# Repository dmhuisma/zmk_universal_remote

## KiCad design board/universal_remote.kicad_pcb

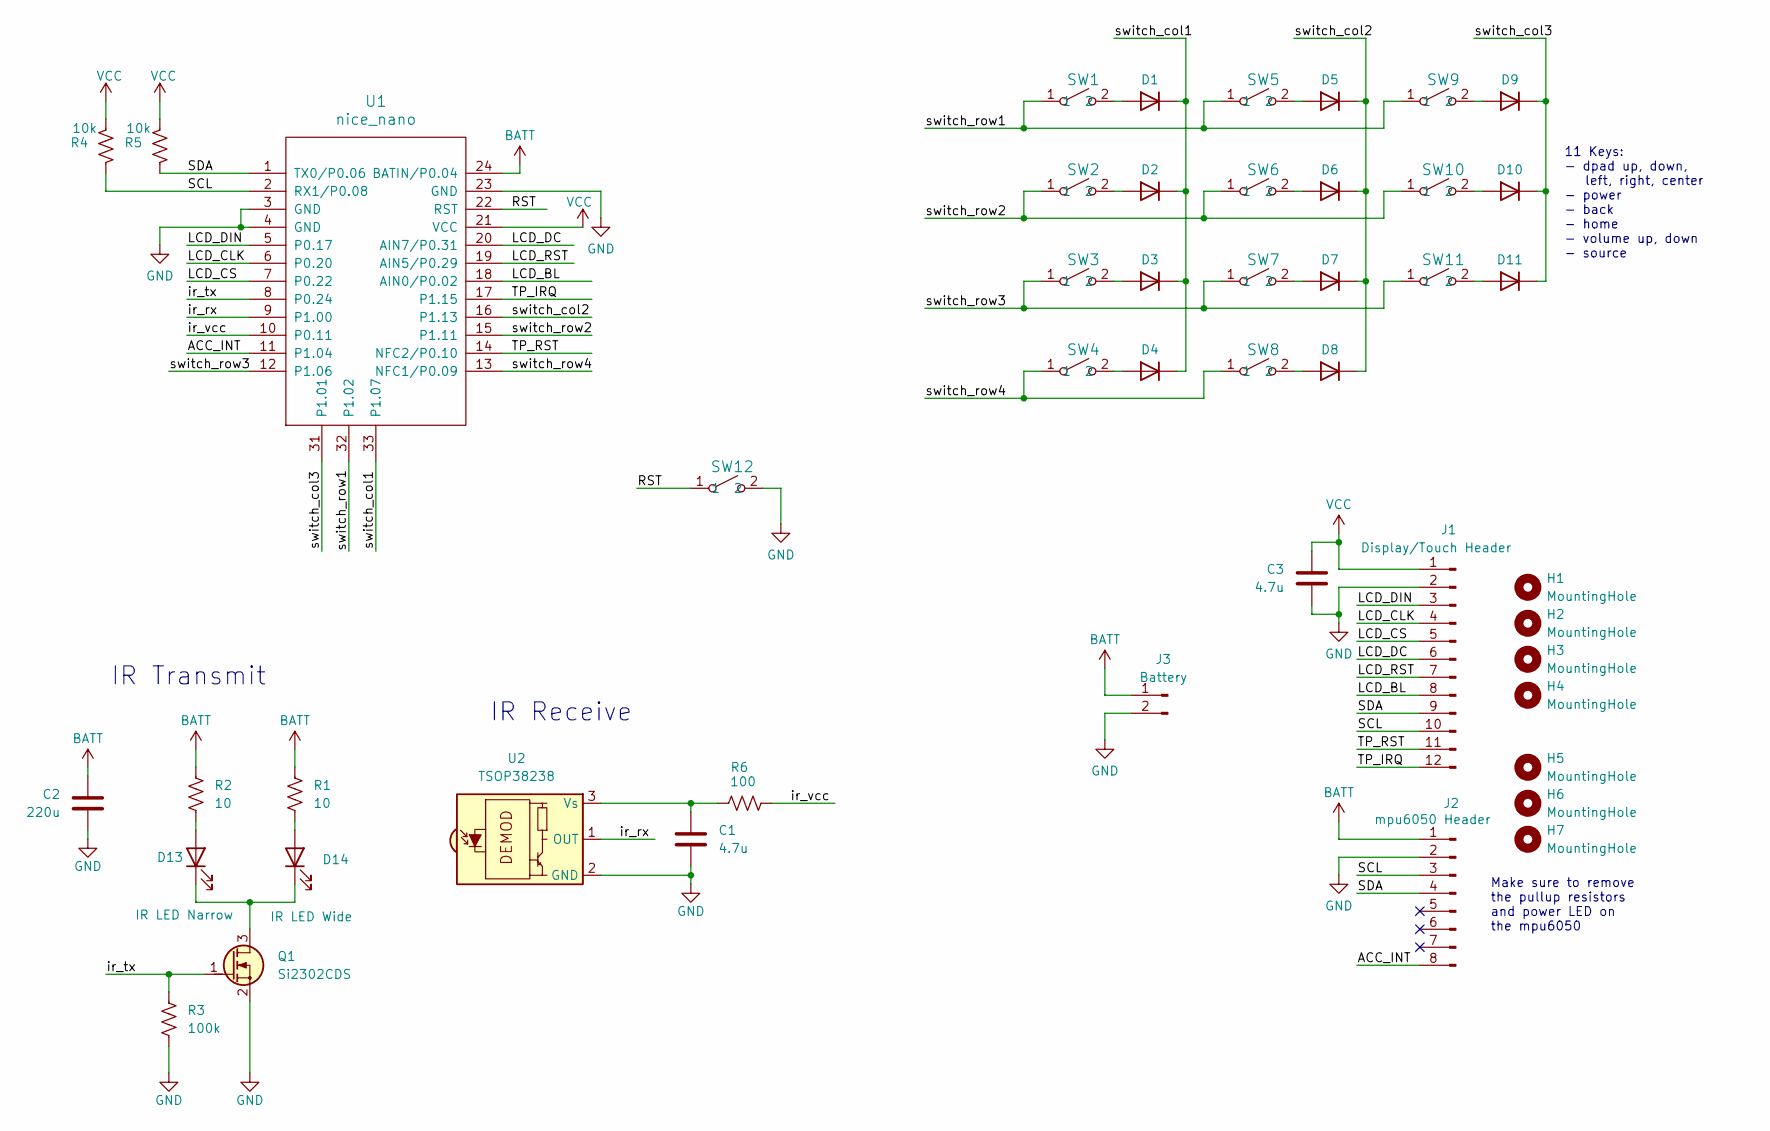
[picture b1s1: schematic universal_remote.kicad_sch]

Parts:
C1, C3: 4.7u; C_0603_1608Metric_Pad1.08x0.95mm_HandSolder
C2: 220u; C_1210_3225Metric_Pad1.33x2.70mm_HandSolder
D1, D2, D3, D4, D5, D6, D7, D8, D9, D10, D11: D; D_DO-35_SOD27_P10.16mm_Horizontal
D13: IR LED Narrow; LED_D5.0mm
D14: IR LED Wide; LED_D5.0mm
H1, H2, H3, H4: MountingHole; MountingHole_2.2mm_M2
H5, H6, H7: MountingHole; MountingHole_3.2mm_M3
J1: Display/Touch Header; PinHeader_1x12_P2.54mm_Vertical
J2: mpu6050 Header; PinHeader_1x08_P2.54mm_Vertical
J3: Battery; PinHeader_1x02_P2.54mm_Vertical
Q1: Si2302CDS; SOT-23
R1, R2: 10; R_1206_3216Metric_Pad1.30x1.75mm_HandSolder
R3: 100k; R_0603_1608Metric_Pad0.98x0.95mm_HandSolder
R4, R5: 10k; R_0603_1608Metric_Pad0.98x0.95mm_HandSolder
R6: 100; R_0603_1608Metric_Pad0.98x0.95mm_HandSolder
SW1, SW2, SW3, SW4, SW5, SW6, SW7, SW8, SW9, SW10, SW11, SW12: SKPMAME010; SKPMAME010_ALPS
U1: nice_nano
U2: TSOP38238; Vishay_MINICAST-3Pin

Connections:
/ACC_INT: J2.8, U1.11 (P1.04)
/LCD_BL: J1.8, U1.18 (AIN0/P0.02)
/LCD_CLK: J1.4, U1.6 (P0.20)
/LCD_CS: J1.5, U1.7 (P0.22)
/LCD_DC: J1.6, U1.20 (AIN7/P0.31)
/LCD_DIN: J1.3, U1.5 (P0.17)
/LCD_RST: J1.7, U1.19 (AIN5/P0.29)
/RST: SW12.1, U1.22 (RST)
/SCL: J1.10, J2.3, R4.2, U1.2 (RX1/P0.08)
/SDA: J1.9, J2.4, R5.2, U1.1 (TX0/P0.06)
/TP_IRQ: J1.12, U1.17 (P1.15)
/TP_RST: J1.11, U1.14 (NFC2/P0.10)
/ir_rx: U1.9 (P1.00), U2.1 (OUT)
/ir_tx: Q1.1 (G), R3.2, U1.8 (P0.24)
/ir_vcc: R6.2, U1.10 (P0.11)
/switch_col1: D1.1 (K), D2.1 (K), D3.1 (K), D4.1 (K), U1.33 (P1.07)
/switch_col2: D5.1 (K), D6.1 (K), D7.1 (K), D8.1 (K), U1.16 (P1.13)
/switch_col3: D9.1 (K), D10.1 (K), D11.1 (K), U1.31 (P1.01)
/switch_row1: SW1.1, SW5.1, SW9.1, U1.32 (P1.02)
/switch_row2: SW2.1, SW6.1, SW10.1, U1.15 (P1.11)
/switch_row3: SW3.1, SW7.1, SW11.1, U1.12 (P1.06)
/switch_row4: SW4.1, SW8.1, U1.13 (NFC1/P0.09)
BATT: C2.2, J2.1, J3.1, R1.1, R2.1, U1.24 (BATIN/P0.04)
GND: C1.2, C2.1, C3.1, J1.2, J2.2, J3.2, Q1.2 (S), R3.1, SW12.2, U1.3 (GND), U1.4 (GND), U1.23 (GND), U2.2 (GND)
unnamed: D1.2 (A), SW1.2
unnamed: D2.2 (A), SW2.2
unnamed: D3.2 (A), SW3.2
unnamed: D4.2 (A), SW4.2
unnamed: D5.2 (A), SW5.2
unnamed: D6.2 (A), SW6.2
unnamed: D7.2 (A), SW7.2
unnamed: D8.2 (A), SW8.2
unnamed: D9.2 (A), SW9.2
unnamed: D10.2 (A), SW10.2
unnamed: D11.2 (A), SW11.2
unnamed: D13.2 (A), R2.2
unnamed: D13.1 (K), D14.1 (K), Q1.3 (D)
unnamed: D14.2 (A), R1.2
unnamed: C1.1, R6.1, U2.3 (Vs)
VCC: C3.2, J1.1, R4.1, R5.1, U1.21 (VCC)

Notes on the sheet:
IR Receive
Make sure to remove the pullup resistors and power LED on the mpu6050
11 Keys: - dpad up, down, left, right, center - power - back - home - volume up, down - source
IR Transmit

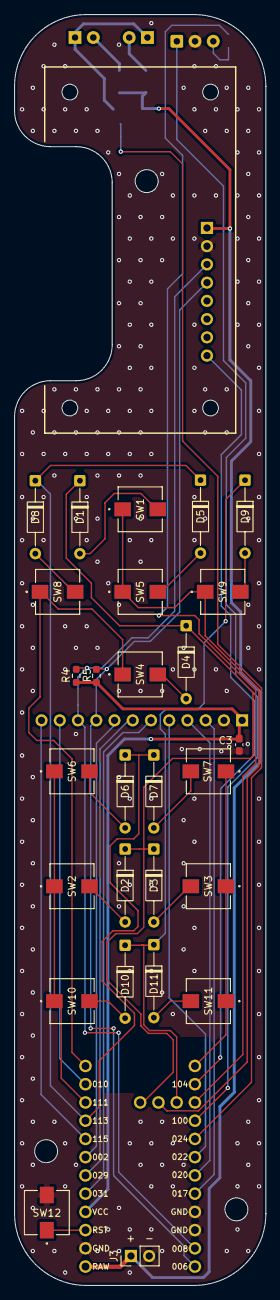
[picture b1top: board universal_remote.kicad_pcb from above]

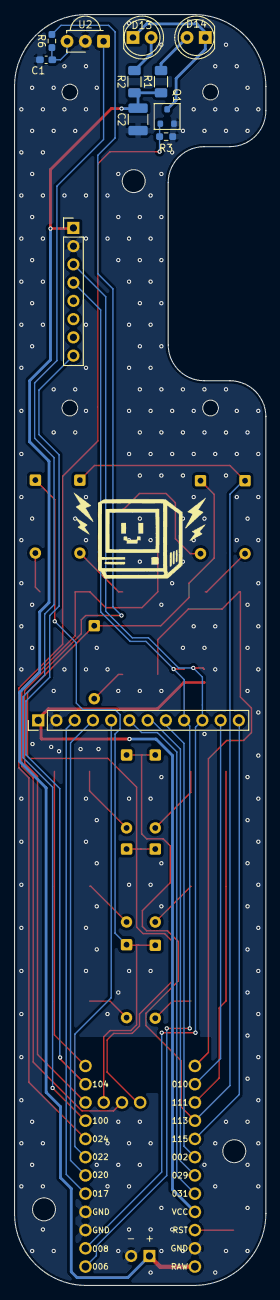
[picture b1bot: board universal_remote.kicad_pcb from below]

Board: 2 copper layers, 35.0 x 177.0 mm, 47 parts (12 on the bottom side), 40 nets.
